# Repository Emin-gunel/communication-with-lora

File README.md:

# LoRa-Pico-BME280

Kısa açıklama  
Raspberry Pi Pico 2 W ve Ai-Thinker RA-01 (SX1278) kullanılarak, BME280 sensöründen alınan sıcaklık/nispi nem/basınç verilerinin LoRa P2P ile diğer bir Pico node'a gönderilip terminalde gösterilmesi amaçlanmıştır. Dengeli, sade ve doğrudan kullanılabilir bir proje yapısı sunar.

---

## İçindekiler
- [Açıklama](#açıklama)  
- [Özellikler](#özellikler)  
- [Donanım](#donanım)  
- [Yazılım Mimarisi](#yazılım-mimarisi)  
- [Haberleşme Parametreleri](#haberleşme-parametreleri)   
- [Çalıştırma / Seri Monitör](#çalıştırma--seri-monitör)  
- [Testler](#testler)  
- [Katkıda Bulunma](#katkıda-bulunma)  
- [İletişim](#iletişim)

---

## Açıklama
Bu proje iki Pico tabanlı node (verici ve alıcı) arasında LoRa P2P haberleşmesi ile sensör verisi aktarımı gerçekleştirir. Verici tarafında BME280 sensöründen okunup paketlenen veriler LoRa ile gönderilir; alıcı tarafı bu paketleri alıp seri (terminal) üzerinde gösterir.

## Özellikler
- Basit P2P LoRa iletişimi (verici ↔ alıcı)  
- BME280 ile sıcaklık, nem ve basınç okuma  
- Taşınabilir C++ tabanlı uygulama (Pico SDK ile C/C++)
  
## Donanım
- Raspberry Pi Pico 2 W (her iki node için)  
- BME280 sensörü (I2C) — verici tarafta  
- AI Thinker RA-01 (SX1278) LoRa modülü — her node için ayrı modül  
- Anten (uygun 433 MHz anten)  
- Güç kaynağı (USB güç)

## Yazılım Mimarisi
- Sensör okuma (BME280, I2C)  
- Veri paketleme (koşullu, küçük paket yapısı)  
- LoRa gönderim (SX1278 üzerinden SPI)  
- RX tarafında alma ve seri terminale yazma

C++ standardı: C++17 (proje C++ ile yazılmıştır).

## Haberleşme Parametreleri
- Frekans: 433 MHz  
- Spreading Factor: SF7  
- Bandwidth: 125 kHz  
- Coding Rate: 4/5  
- TX Gücü: 17 dBm

Bu parametreler LoRa link'i ve menzili doğrudan etkiler — gerekirse ayarlanabilir.

## Çalıştırma / Seri Monitör
- Seri hız: 115200 baud (varsayılan; proje içinde değiştirilebilir).  
- Terminal ile izleme örneği:

```bash
# Linux / macOS
picocom /dev/ttyUSB0 -b 115200
# veya
minicom -D /dev/ttyUSB0 -b 115200
```
Verici: sensör verilerini periyodik olarak paket gönderir.  
Alıcı: gelen paketları çözümler ve terminale yazdırır.

## Testler
- Projede otomatik test altyapısı yoksa, ilk testler manuel olacaktır: verici ve alıcıyı aynı ortamda çalıştırıp, sensör okuma ve paket alımını doğrulayın.  
- Bir sonraki adım: basit bir loopback testi ve menzil testi yapmaktır (farklı mesafeler/engeller altında paket kaybını kontrol edin).

## Katkıda Bulunma
1. Fork → branch oluştur (ör. feature/iyileme-adi)  
2. Değişiklik yap → test et → PR aç  
3. Küçük, odaklı PR'lar tercih edilir; büyük değişiklikler için önce issue açın.

## İletişim
- Sahip / Repo: https://github.com/Emin-gunel (güncellemek isterseniz gerçek repo linkinizi ekleyin)

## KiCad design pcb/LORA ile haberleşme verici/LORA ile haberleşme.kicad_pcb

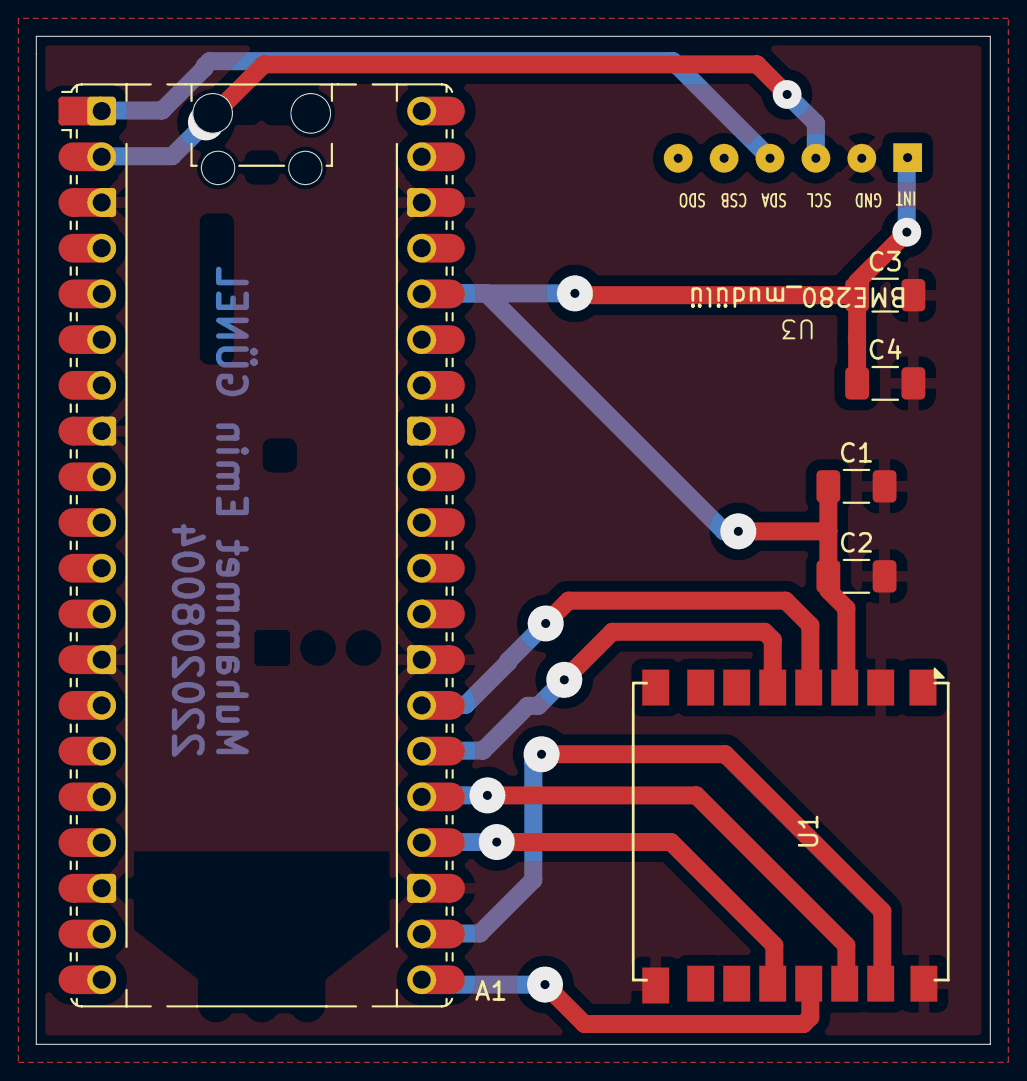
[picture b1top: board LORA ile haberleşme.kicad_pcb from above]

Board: 4 copper layers, 53.0 x 56.0 mm, 7 parts (0 on the bottom side), 10 nets.

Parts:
A1: RaspberryPi_Pico_W; RaspberryPi_Pico_Common_Unspecified
C1, C3: 100n; C_1206_3216Metric_Pad1.33x1.80mm_HandSolder
C2, C4: 10u; C_1206_3216Metric_Pad1.33x1.80mm_HandSolder
U1: Ai-Thinker-Ra-01; Ai-Thinker-Ra-01-LoRa
U3: BME280_mudülü; Untitled

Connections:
3.3V: A1.36 (3V3), C1.1, C2.1, C3.1, C4.1, U1.3 (VDD), U3.1 (VCC)
GND: A1.3 (GND), A1.8 (GND), A1.13 (GND), A1.18 (GND), A1.23 (GND), A1.28 (GND), A1.38 (GND), C1.2, C2.2, C3.2, C4.2, U1.2 (GND), U1.9 (GND), U1.16 (GND), U3.6 (GND)
unnamed: A1.1 (GPIO0), U3.3 (SDA)
unnamed: A1.2 (GPIO1), U3.2 (SCL)
unnamed: A1.21 (GPIO16), U1.13 (MISO)
unnamed: A1.22 (GPIO17), U1.15 (~NSS)
unnamed: A1.24 (GPIO18), U1.12 (SCK)
unnamed: A1.25 (GPIO19), U1.14 (MOSI)
unnamed: A1.26 (GPIO20), U1.5 (DIO0)
unnamed: A1.27 (GPIO21), U1.4 (~RESET)

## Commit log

2025-11-03 MyFirstMessage
2025-11-29 Alıcı ve Verici PCB dosyaları eklendi
2025-12-25 Add PCB, firmware, report and README
2025-12-27 Update README.md — LoRa-Pico-BME280
2025-12-27 Son degisiklikler
2025-12-27 RREADME dosyası revize edildi
2025-12-27 Update README.md — content revisions
2025-12-27 README revize edildi
2026-01-05 Rapor güncellendi
2026-01-05 Test Prosedürleri yüklendi
2026-01-05 Test prosedürleri güncellendi
